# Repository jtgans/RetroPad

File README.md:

# RetroPad v2.0

## What is this?

This is an open source Commodore compatible gamepad similar in design to a
Genesis or NES gamepad, but designed specifically for the Commodore and Atari
8-bit machines prior to the Amigas.

This project is part of the [Nybbles and Bytes Commodore 128D programming
series](http://youtube.com/nybblesandbytes).

## Why make this?

The author needed a joystick for her YouTube project, [Nybbles and
Bytes](http://youtube.com/nybblesandbytes) and felt that joysticks were too
imprecise, troublesome, and wanted something more accessible. Gamepads fit the
bill, but Master System and Genesis controllers used the wrong electricals and
could cause damage to her systems.

## Which computers is this compatible with?

The author has tested the initial prototype with a Commodore 128D, but
electrically RetroPad should be compatible with any machines that support
floating logic level inputs that are expected to be shorted to ground when the
switches are closed (open-drain configuration, similar to I2C). This basically
means it should theoretically work on the following machines:

  - Commodore VIC-20
  - Commodore 64
  - Commodore 128, 128D, 128DCR, etc.
  - Atari 2600, 7800, etc.
  - Atari ST*

## How was this made?

The schematics were put together using KiCad 5.0 on a Mac. This should be
cross-compatible with any other platform KiCad 5.0 runs on. The author used the
[DigiKey KiCad Libraries](https://github.com/Digi-Key/digikey-kicad-library) to
simplify footprint and symbol selection, so you'll want to download those and
set them up globally. They were not included in this project repository as
project-specific since that would effectively constitute a fork or
redistribution which would then require their licensing. Plus, the project
wouldn't get any updated footprints.

The STL files and models of the casing were designed publicly using the
parametric modelling tool, OnShape. FreeCAD was originally considered, but
unfortunately it's been too unstable for the author to use thus far.

You can get to the RetroPad Shell
project
[in OnShape here](https://cad.onshape.com/documents/0ce2d4035447341de67353ed/w/eda42658079851fc0d119e48/e/4d807dce885e1d6fdc5af67c).

Search for "RetroPad" in the public models archive and you can get the source
models straight from there. For folks preferring to use a different modelling
program, the STL files are also available with the schematics in this
repository under
the [case/ directory](https://github.com/jtgans/RetroPad/tree/master/case).

The "RetroPad.step" file is actually just the 3D rendering of the PCBA.

## Where is the BOM?

The BOM is very very simple at the moment, basically only using Omron B3F-1000
tactile switches straight from Digikey. Any 8mm pitch tactile switch with a
similar profile to the B3F-1000 should work.

The connection to the computer is made using a 9-pin D-Sub connector. Any
straight-through female to female 9-pin serial cable should work, supposing the
housing allows for it.

Assembly is super easy since it's all through hole parts and two very large 0608
SMD resistors.

The generated BOM is available in the CSV file in this repository, but an actual
BOM ordered by the author is available in the digikey.csv file.

## How should I fab the PCB?

The author prefers to use OSHPark as the PCB fab house of choice, though with
some finagling you could easily adapt to other providers such as PCBWay or
others.

The original PCB is
available [on oshpark here](https://oshpark.com/shared_projects/t22Mpv2t).

## How should I fab the case?

The author used her Prusa i3 Mk3s FDM 3D printer with a 0.2mm layer height and
no support to print out the case. The model requires a high degree of precision
in the printer, with a 0.1mm tolerance between the fire and jump buttons and the
top half of the shell. The D-Pad area requires at least 0.5mm tolerance. You may
have to file the parts down a small amount, depending on the resolution and
precision of your printer.

Note that the case is designed to hold together using friction, so no fasteners
are necessary. Also note that in the v1.1 design, there's not quite enough of a
cutout for the cable strain relief to fit, so it may bow out a small amount.

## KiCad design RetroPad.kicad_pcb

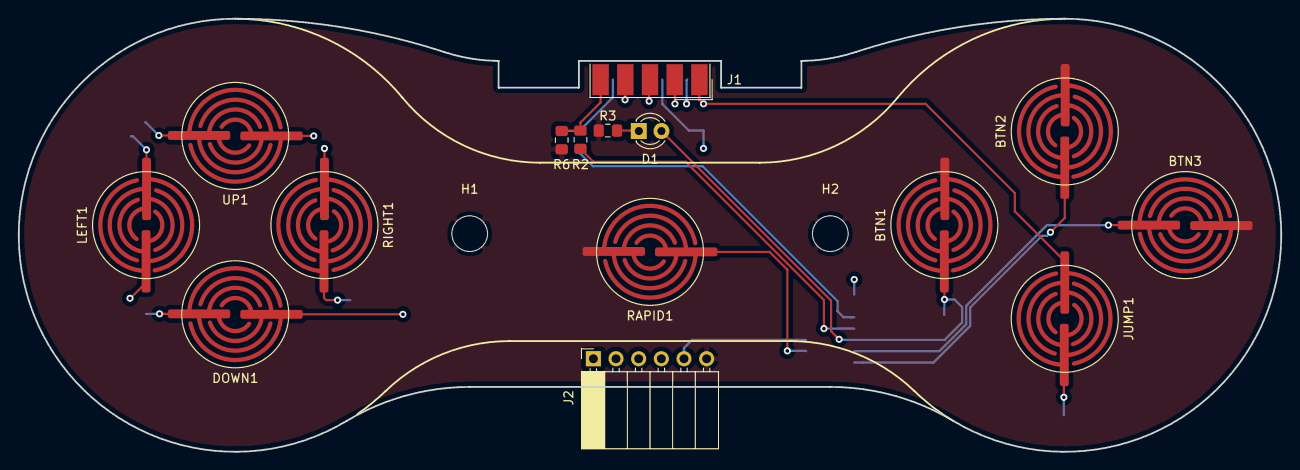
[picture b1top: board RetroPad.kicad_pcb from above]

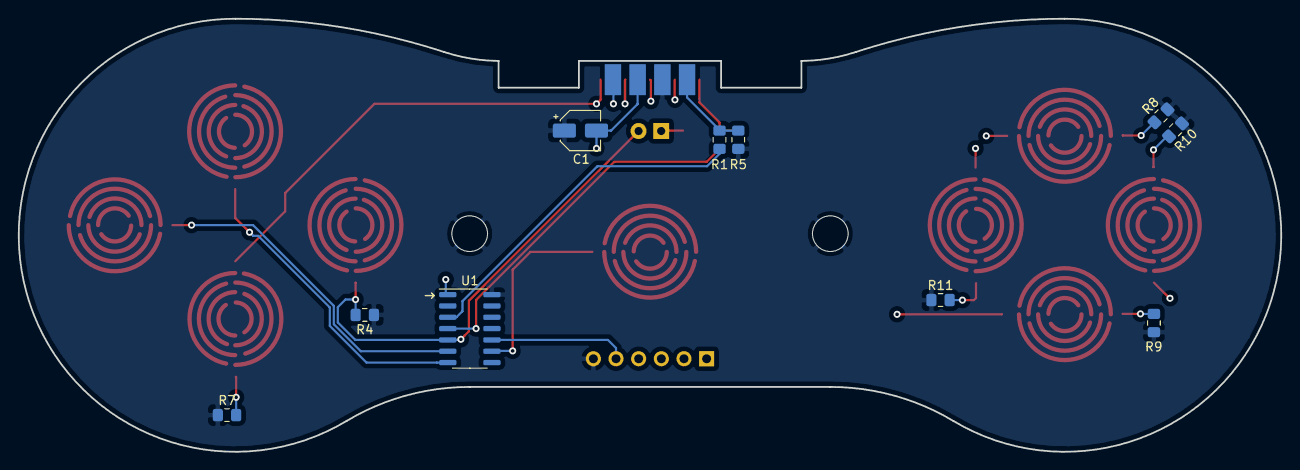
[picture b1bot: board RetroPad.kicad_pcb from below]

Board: 4 copper layers, 141.6 x 48.6 mm, 27 parts (10 on the bottom side), 21 nets.

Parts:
BTN1: BTN1; Silicone_Membrane_Pad_11mm_(7.5mm)
BTN2: BTN2; Silicone_Membrane_Pad_11mm_(7.5mm)
BTN3: BTN3; Silicone_Membrane_Pad_11mm_(7.5mm)
C1: 0.1uF; CP_Elec_4x4.5
D1: RAPID; LED_D3.0mm
DOWN1: DOWN; Silicone_Membrane_Pad_11mm_(7.5mm)
H1, H2: MountingHole; MountingHole_4mm
J1: DB9_Male; DSUB-9_Male_EdgeMount_P2.77mm
J2: UPDI; PinSocket_1x06_P2.54mm_Horizontal
JUMP1: JUMP; Silicone_Membrane_Pad_11mm_(7.5mm)
LEFT1: LEFT; Silicone_Membrane_Pad_11mm_(7.5mm)
R1, R2, R4, R5, R6: 1K; R_0805_2012Metric_Pad1.15x1.40mm_HandSolder
R3: 330; R_0805_2012Metric_Pad1.15x1.40mm_HandSolder
R7, R8, R9, R10, R11: 0; R_0805_2012Metric_Pad1.15x1.40mm_HandSolder
RAPID1: RAPID; Silicone_Membrane_Pad_11mm_(7.5mm)
RIGHT1: RIGHT; Silicone_Membrane_Pad_11mm_(7.5mm)
U1: ATtiny814-SS; SOIC-14_3.9x8.7mm_P1.27mm
UP1: UP; Silicone_Membrane_Pad_11mm_(7.5mm)

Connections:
+5V: C1.2, J1.7, J2.4, U1.1
/BTN2: BTN2.2, U1.7
/BTN3: BTN3.2, U1.6
/DOWN: DOWN1.2, J1.2
/FIRE: BTN1.2, D1.2, J1.6, R4.2, U1.5
/LEFT: J1.3, LEFT1.2
/OUT_BTN2: R2.2, U1.4
/OUT_BTN3: R1.2, U1.3
/POTX: J1.9, R1.1, R5.2
/POTY: J1.5, R2.1, R6.2
/RAPID: RAPID1.2, U1.9
/RESET: J2.5, U1.10
/RIGHT: J1.4, RIGHT1.2
/UP: J1.1, JUMP1.2, UP1.2
GND: BTN1.1, BTN2.1, BTN3.1, C1.1, H1.1, H2.1, J1.8, J2.6, R3.1, R4.1, R5.1, R6.1, R7.1, R8.1, R9.1, R10.1, R11.1, RAPID1.1, U1.14
unnamed: D1.1, R3.2
unnamed: DOWN1.1, R9.2
unnamed: JUMP1.1, R7.2
unnamed: LEFT1.1, R10.2
unnamed: R8.2, UP1.1
unnamed: R11.2, RIGHT1.1

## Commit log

2019-04-13 Initial commit for RetroPad v1.1.
2019-04-13 readme: Minor addendum -- no support.
2019-04-19 Fix the readme.
2019-04-19 pcb: Major revision to mechanicals
    This is a near total redesign of the RetroPad. Electrically it should be
    identical, aside from two additional buttons. Major features planned are:
    - Two additional fire buttons using POTX and POTY for games that support it.
    - Migrates from raw-through hole wiring to a proper male 9-pin D-Sub
    connector. This should be significantly more robust.
    - Mechanical redesign of the positioning for the buttons and D-pad.
2019-04-19 docs: Update the README and add a Digikey BOM
2019-04-19 pcb: Add 3D models for the FIRE2 and FIRE3 buttons
2019-04-19 Add in the GPLv2 license
2019-04-19 Add in the GPLv2 license
    (cherry picked from commit 7a8cb96a4eb4ffbc2509e6cf39045385ca98eacf)
2019-04-19 readme: Add in a picture of the model
2019-04-19 readme: Add in a picture of the model
    (cherry picked from commit 3c70ab65fbfdfb1611db820755f111fe3201be03)
2019-04-19 readme: Update to match the new revision
2019-04-19 readme: Add a warning about fabbing v2
2019-04-19 readme: Update the OshPark link to the v1.1 release
2019-04-19 readme: Tweaks to the statement about the 3D models
2019-04-19 readme: Tweaks to the statement about the 3D models
    (cherry picked from commit c1ce28cc094c0c2ce5d34b186401f2c284bfcb03)
2019-04-19 readme: Update with information about libraries
    This project uses the DigiKey libraries for KiCad to simplify things, so we
    should mention that to folks beforehand.
2019-04-19 ignore: Stop watching fp-info-cache files
2019-04-19 pcb: Refill the copper pours
2019-04-19 readme: Note that the project came from Nybbles and Bytes
2019-04-19 ignore: Stop watching fp-info-cache files
    (cherry picked from commit 5df439567b466adf7c73675561d9a09f03a4a703)
2019-04-19 readme: Update with information about libraries
    This project uses the DigiKey libraries for KiCad to simplify things, so we
    should mention that to folks beforehand.
    (cherry picked from commit 3f0ea1ff78b1fd4a1acff8641a87dd14f6e8ecf3)
2019-04-19 readme: Note that the project came from Nybbles and Bytes
    (cherry picked from commit d94c44edfb34b86917ecbf142e7c68109c869185)
2019-04-19 models: Remove the CK Switches 3D model since it's unused
2019-04-19 models: Remove the CK Switches 3D model since it's unused
    (cherry picked from commit a524397730d8e2f880d0adf93546dc6aa7588099)
2019-04-20 bom: Unify the BOM CSV so it renders cleanly
2019-04-20 step: Regenerate for v2.0 with the D-Sub connector in place
2019-04-20 case: Update the case to the new design
    This brings in all the STL files from the new design as well as a pre-rendered
    image of the new case.
2019-04-20 readme: Update the pre-rendered image location
2019-04-27 artifacts: Generate PDFs of the current schematic and board art
2019-04-27 kicad: Update project file
    This includes additional metadata about the schematic editor
    after printing out the PDF of the RetroPad schematic.
2019-05-17 case: Update the STL files and pre-rendered image
2019-05-17 readme: Remove the v2.0 warning
2020-04-07 Import of the new RetroPad v3.
2020-04-07 Fixed board outline.
